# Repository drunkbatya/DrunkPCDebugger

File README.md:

# DrunkPC Debugger
A debugger and flasher for [DrunkPC](https://github.com/drunkbatya/DrunkPC)

<picture>
    
</picture>

## How to use

## How to build firmware

## How to cli tool

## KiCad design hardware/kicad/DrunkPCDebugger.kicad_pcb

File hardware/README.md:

## Errata
### Rev1
`MCU_BUS_DIR` and `BUS_OE\` shared across all 4 transivers, this prevents reading compleately, need to separate

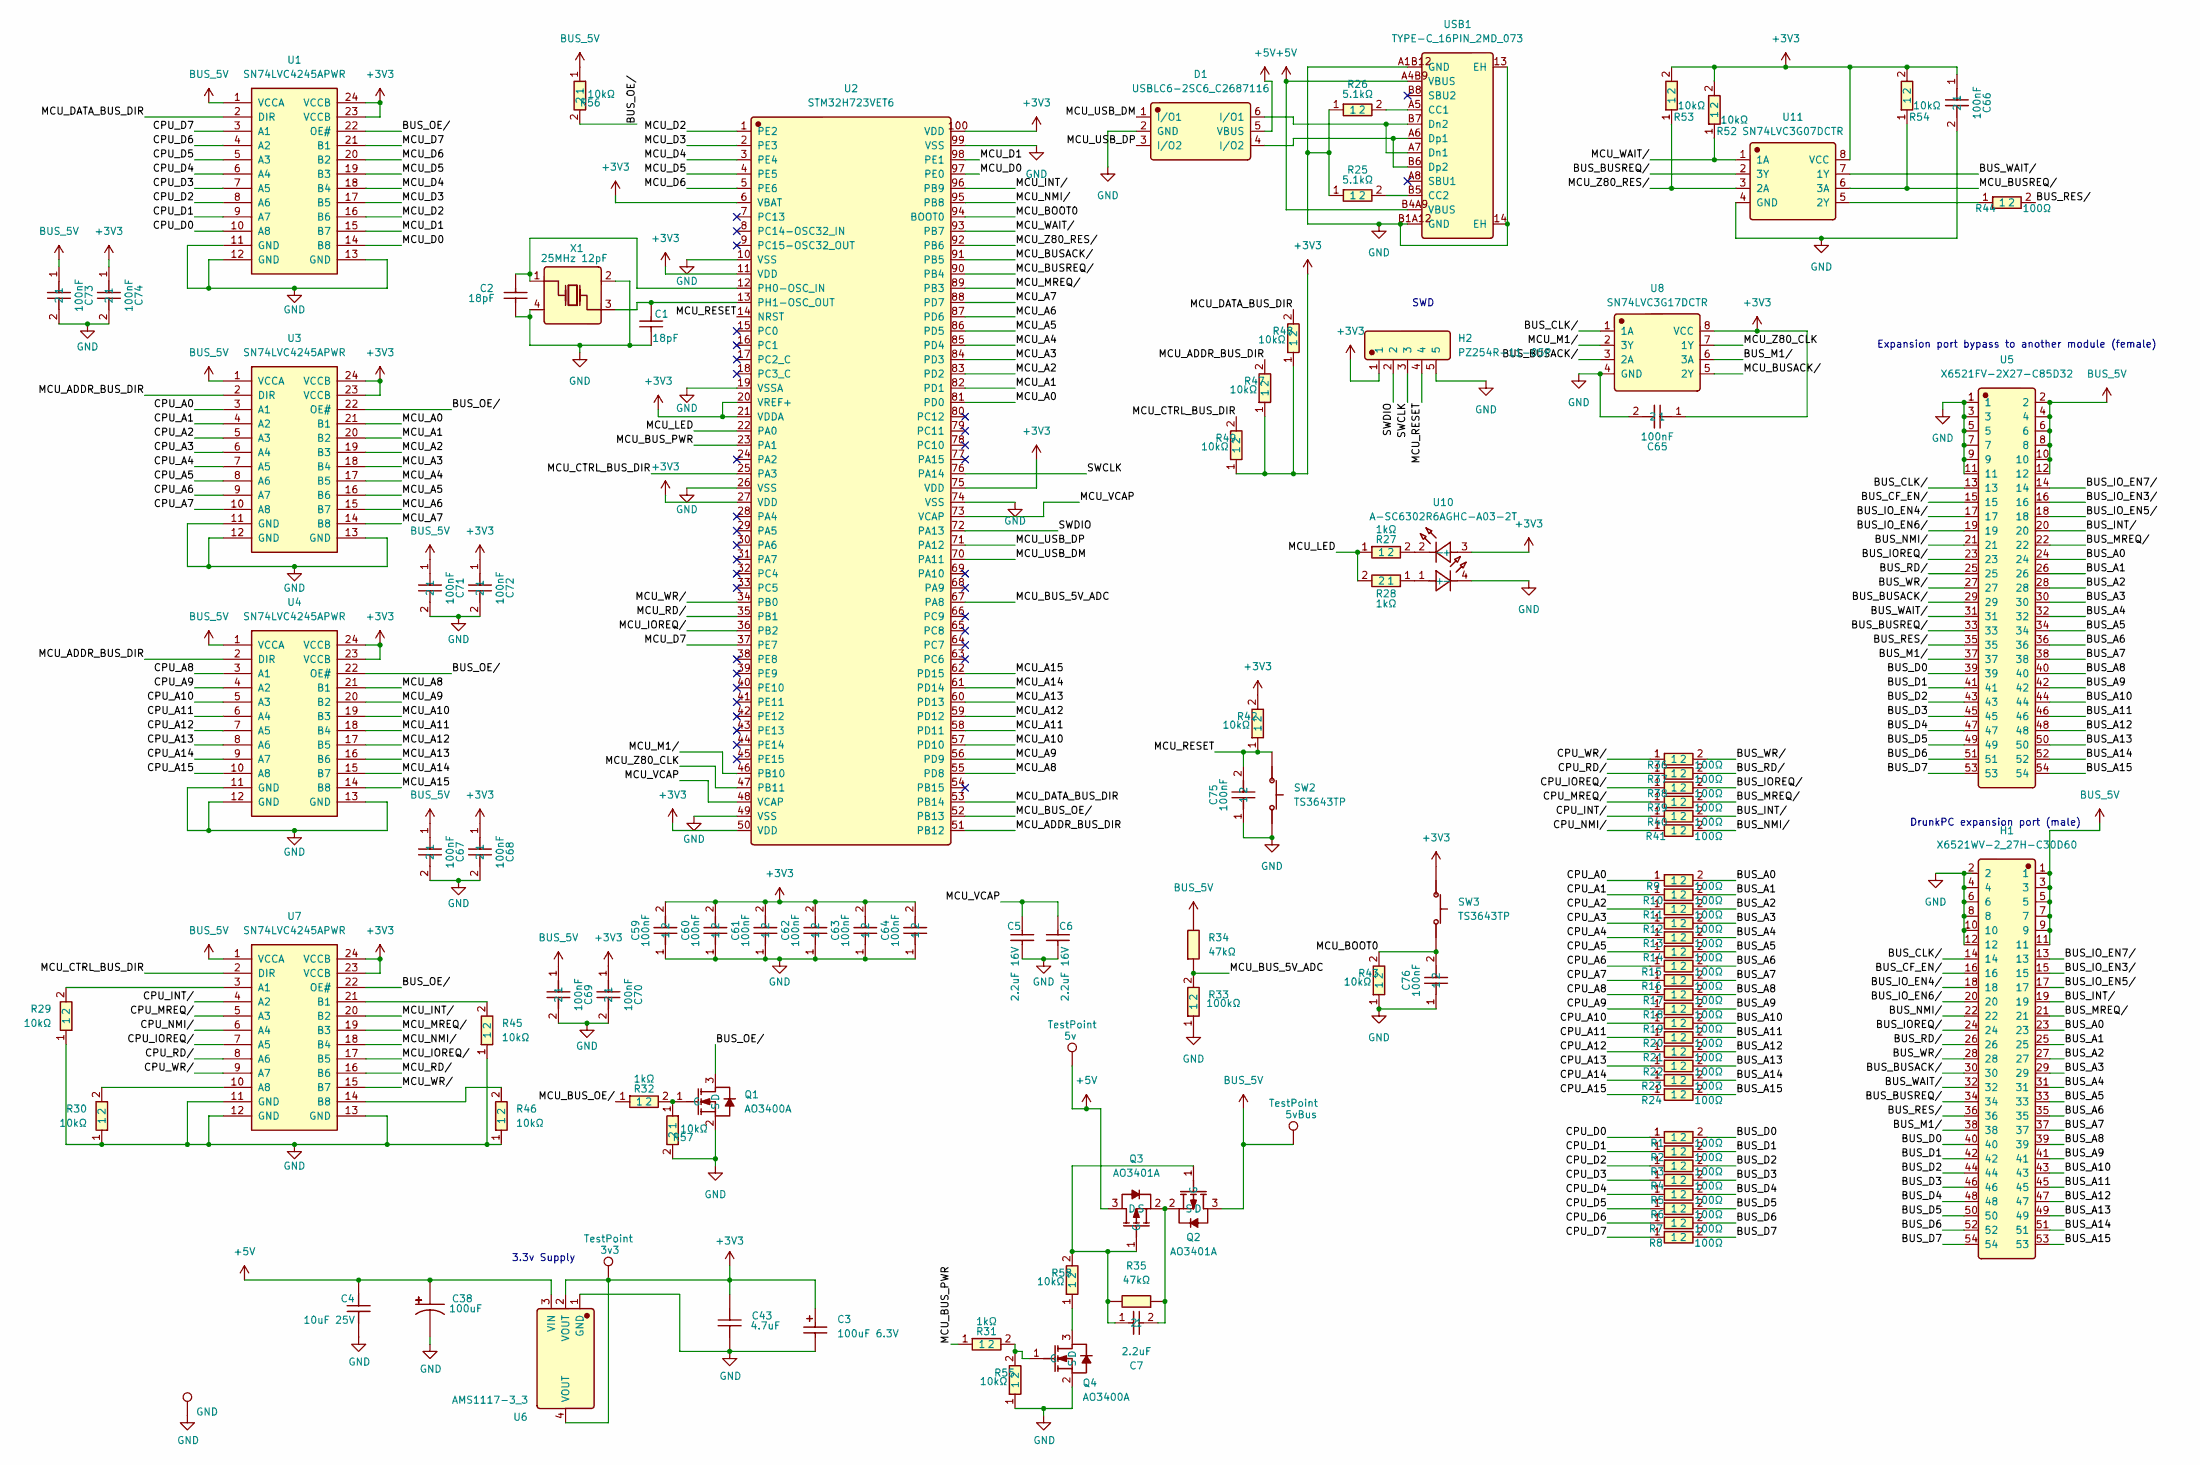
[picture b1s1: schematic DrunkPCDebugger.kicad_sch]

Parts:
3v3_1: 3v3; TestPoint_Pad_D1.5mm
5v_1: 5v; TestPoint_Pad_D1.5mm
5v_bus_1: 5vBus; TestPoint_Pad_D1.5mm
C1, C2: CL10C180JB8NNNC; C_0603_1608Metric; Manufacturer Part CL10C180JB8NNNC; LCSC C1647
C3: 100uF 6.3V; CP_EIA-3528-21_Kemet-B; Manufacturer Part TAJB107K006RNJ; LCSC C16133
C4: 10uF 25V; C_0805_2012Metric; Manufacturer Part CL21A106KAYNNNE; LCSC C15850
C5, C6: 2.2uF 16V; C_0603_1608Metric; Manufacturer Part CL10A225KO8NNNC; LCSC C23630
C7: 2.2uF; C_0603_1608Metric; Manufacturer Part CL10A225KO8NNNC; LCSC C23630
C38: EEFCX0J101R; Manufacturer Part EEFCX0J101R; LCSC C189619
C43: CL10A475KO8NNNC; C_0603_1608Metric; Manufacturer Part CL10A475KO8NNNC; LCSC C19666
C59, C60, C61, C62, C63, C64, C65, C66, C67, C68, C69, C70, C71, C72, C73, C74, C75, C76: CC0603KRX7R9BB104; C_0603_1608Metric; Manufacturer Part CC0603KRX7R9BB104; LCSC C14663
D1: USBLC6-2SC6_C2687116; Manufacturer Part USBLC6-2SC6; LCSC C2687116
GND1: GND; TestPoint_Pad_2.0x2.0mm
H1: X6521WV-2_27H-C30D60; Manufacturer Part X6521WV-2x27H-C60D30; LCSC C725899
H2: PZ254R-11-05P; Manufacturer Part PZ254R-11-05P; LCSC C492413
Q1, Q4: AO3400A; Manufacturer Part AO3400A; LCSC C20917
Q2, Q3: AO3401A; Manufacturer Part AO3401A; LCSC C15127
R1, R2, R3, R4, R5, R6, R7, R8, R9, R10, R11, R12, R13, R14, R15, R16, R17, R18, R19, R20, R21, R22, R23, R24, R36, R37, R38, R39, R40, R41, R44: 0603WAF1000T5E; R_0603_1608Metric; Manufacturer Part 0603WAF1000T5E; LCSC C22775
R25, R26: 0603WAF5101T5E; R_0603_1608Metric; Manufacturer Part 0603WAF5101T5E; LCSC C23186
R27, R28, R31, R32: 0603WAF1001T5E; R_0603_1608Metric; Manufacturer Part 0603WAF1001T5E; LCSC C21190
R29, R30, R45, R46: 10kΩ; R_0603_1608Metric; Manufacturer Part 0603WAF1002T5E; LCSC C25804
R33: 0603WAF1003T5E; R_0603_1608Metric; Manufacturer Part 0603WAF1003T5E; LCSC C25803
R34, R35: 47kΩ; R_0603_1608Metric; Manufacturer Part 0603WAF4702T5E; LCSC C25819
R42, R43, R47, R48, R49, R52, R53, R54, R55, R56, R57, R58: 0603WAF1002T5E; R_0603_1608Metric; Manufacturer Part 0603WAF1002T5E; LCSC C25804
SW2, SW3: TS3643TP; Manufacturer Part TS3643TP; LCSC C398054
U1, U3, U4, U7: SN74LVC4245APWR; Manufacturer Part SN74LVC4245APWR; LCSC C7859
U2: STM32H723VET6; Manufacturer Part STM32H723VET6; LCSC C730141
U5: X6521FV-2X27-C85D32; Manufacturer Part X6521FV-2x27-C85D32; LCSC C2884000
U6: AMS1117-3_3; Manufacturer Part AMS1117-3.3; LCSC C6186
U8: SN74LVC3G17DCTR; Manufacturer Part SN74LVC3G17DCTR; LCSC C18213
U10: A-SC6302R6AGHC-A03-2T; Manufacturer Part A-SC6302R6AGHC-A03-2T; LCSC C5355456
U11: SN74LVC3G07DCTR; Manufacturer Part SN74LVC3G07DCTR; LCSC C131914
USB1: TYPE-C_16PIN_2MD_073; Manufacturer Part TYPE-C 16PIN 2MD(073); LCSC C2765186
X1: X322525MOB4SI; Crystal_SMD_3225-4Pin_3.2x2.5mm; Manufacturer Part X322525MOB4SI; LCSC C9006

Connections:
+3V3: 3v3_1.1 (1_1), C3.1, C43.2, C59.2, C60.2, C61.2, C62.2, C63.2, C64.2, C65.1, C66.1, C68.1, C70.1, C72.1, C74.1, H2.1, R42.2, R47.1, R48.1, R49.1, R52.2, R53.2, R54.2, SW3.1, U1.23 (VCCB), U1.24 (VCCB), U2.6 (VBAT), U2.11 (VDD), U2.20 (VREF+), U2.21 (VDDA), U2.27 (VDD), U2.50 (VDD), U2.75 (VDD), U2.100 (VDD), U3.23 (VCCB), U3.24 (VCCB), U4.23 (VCCB), U4.24 (VCCB), U6.2 (VOUT), U6.4 (VOUT), U7.23 (VCCB), U7.24 (VCCB), U8.8 (VCC), U10.3 (+), U11.8 (VCC)
+5V: 5v_1.1 (1_1), C4.1, C38.1, D1.5 (VBUS), Q3.3 (D), U6.3 (VIN), USB1.A4B9 (VBUS), USB1.B4A9 (VBUS)
/BUS_A0: H1.23, R9.2, U5.24
/BUS_A1: H1.25, R10.2, U5.26
/BUS_A2: H1.27, R11.2, U5.28
/BUS_A3: H1.29, R12.2, U5.30
/BUS_A4: H1.31, R13.2, U5.32
/BUS_A5: H1.33, R14.2, U5.34
/BUS_A6: H1.35, R15.2, U5.36
/BUS_A7: H1.37, R16.2, U5.38
/BUS_A8: H1.39, R17.2, U5.40
/BUS_A9: H1.41, R18.2, U5.42
/BUS_A10: H1.43, R19.2, U5.44
/BUS_A11: H1.45, R20.2, U5.46
/BUS_A12: H1.47, R21.2, U5.48
/BUS_A13: H1.49, R22.2, U5.50
/BUS_A14: H1.51, R23.2, U5.52
/BUS_A15: H1.53, R24.2, U5.54
/BUS_BUSACK/: H1.30, U5.29, U8.3 (2A)
/BUS_BUSREQ/: H1.34, U5.33, U11.2 (3Y)
/BUS_CF_EN/: H1.16, U5.15
/BUS_CLK/: H1.14, U5.13, U8.1 (1A)
/BUS_D0: H1.40, R1.2, U5.39
/BUS_D1: H1.42, R2.2, U5.41
/BUS_D2: H1.44, R3.2, U5.43
/BUS_D3: H1.46, R4.2, U5.45
/BUS_D4: H1.48, R5.2, U5.47
/BUS_D5: H1.50, R6.2, U5.49
/BUS_D6: H1.52, R7.2, U5.51
/BUS_D7: H1.54, R8.2, U5.53
/BUS_INT/: H1.19, R40.2, U5.20
/BUS_IOREQ/: H1.24, R38.2, U5.23
/BUS_IO_EN3/: H1.15, U5.16
/BUS_IO_EN4/: H1.18, U5.17
/BUS_IO_EN5/: H1.17, U5.18
/BUS_IO_EN6/: H1.20, U5.19
/BUS_IO_EN7/: H1.13, U5.14
/BUS_M1/: H1.38, U5.37, U8.6 (3A)
/BUS_MREQ/: H1.21, R39.2, U5.22
/BUS_NMI/: H1.22, R41.2, U5.21
/BUS_OE/: Q1.3 (D), R56.2, U1.22 (OE#), U3.22 (OE#), U4.22 (OE#), U7.22 (OE#)
/BUS_RD/: H1.26, R37.2, U5.25
/BUS_RES/: H1.36, R44.2, U5.35
/BUS_WAIT/: H1.32, U5.31, U11.7 (1Y)
/BUS_WR/: H1.28, R36.2, U5.27
/CPU_A0: R9.1, U3.3 (A1)
/CPU_A1: R10.1, U3.4 (A2)
/CPU_A2: R11.1, U3.5 (A3)
/CPU_A3: R12.1, U3.6 (A4)
/CPU_A4: R13.1, U3.7 (A5)
/CPU_A5: R14.1, U3.8 (A6)
/CPU_A6: R15.1, U3.9 (A7)
/CPU_A7: R16.1, U3.10 (A8)
/CPU_A8: R17.1, U4.3 (A1)
/CPU_A9: R18.1, U4.4 (A2)
/CPU_A10: R19.1, U4.5 (A3)
/CPU_A11: R20.1, U4.6 (A4)
/CPU_A12: R21.1, U4.7 (A5)
/CPU_A13: R22.1, U4.8 (A6)
/CPU_A14: R23.1, U4.9 (A7)
/CPU_A15: R24.1, U4.10 (A8)
/CPU_D0: R1.1, U1.10 (A8)
/CPU_D1: R2.1, U1.9 (A7)
/CPU_D2: R3.1, U1.8 (A6)
/CPU_D3: R4.1, U1.7 (A5)
/CPU_D4: R5.1, U1.6 (A4)
/CPU_D5: R6.1, U1.5 (A3)
/CPU_D6: R7.1, U1.4 (A2)
/CPU_D7: R8.1, U1.3 (A1)
/CPU_INT/: R40.1, U7.4 (A2)
/CPU_IOREQ/: R38.1, U7.7 (A5)
/CPU_MREQ/: R39.1, U7.5 (A3)
/CPU_NMI/: R41.1, U7.6 (A4)
/CPU_RD/: R37.1, U7.8 (A6)
/CPU_WR/: R36.1, U7.9 (A7)
/MCU_A0: U2.81 (PD0), U3.21 (B1)
/MCU_A1: U2.82 (PD1), U3.20 (B2)
/MCU_A2: U2.83 (PD2), U3.19 (B3)
/MCU_A3: U2.84 (PD3), U3.18 (B4)
/MCU_A4: U2.85 (PD4), U3.17 (B5)
/MCU_A5: U2.86 (PD5), U3.16 (B6)
/MCU_A6: U2.87 (PD6), U3.15 (B7)
/MCU_A7: U2.88 (PD7), U3.14 (B8)
/MCU_A8: U2.55 (PD8), U4.21 (B1)
/MCU_A9: U2.56 (PD9), U4.20 (B2)
/MCU_A10: U2.57 (PD10), U4.19 (B3)
/MCU_A11: U2.58 (PD11), U4.18 (B4)
/MCU_A12: U2.59 (PD12), U4.17 (B5)
/MCU_A13: U2.60 (PD13), U4.16 (B6)
/MCU_A14: U2.61 (PD14), U4.15 (B7)
/MCU_A15: U2.62 (PD15), U4.14 (B8)
/MCU_ADDR_BUS_DIR: R47.2, U2.51 (PB12), U3.2 (DIR), U4.2 (DIR)
/MCU_BOOT0: C76.2, R43.2, SW3.2, U2.94 (BOOT0)
/MCU_BUSACK/: U2.91 (PB5), U8.5 (2Y)
/MCU_BUSREQ/: R54.1, U2.90 (PB4), U11.6 (3A)
/MCU_BUS_5V_ADC: R33.2, R34.1, U2.67 (PA8)
/MCU_BUS_OE/: R32.1, U2.52 (PB13)
/MCU_BUS_PWR: R31.1, U2.23 (PA1)
/MCU_CTRL_BUS_DIR: R49.2, U2.25 (PA3), U7.2 (DIR)
/MCU_D0: U1.14 (B8), U2.97 (PE0)
/MCU_D1: U1.15 (B7), U2.98 (PE1)
/MCU_D2: U1.16 (B6), U2.1 (PE2)
/MCU_D3: U1.17 (B5), U2.2 (PE3)
/MCU_D4: U1.18 (B4), U2.3 (PE4)
/MCU_D5: U1.19 (B3), U2.4 (PE5)
/MCU_D6: U1.20 (B2), U2.5 (PE6)
/MCU_D7: U1.21 (B1), U2.37 (PE7)
/MCU_DATA_BUS_DIR: R48.2, U1.2 (DIR), U2.53 (PB14)
/MCU_INT/: U2.96 (PB9), U7.20 (B2)
/MCU_IOREQ/: U2.36 (PB2), U7.17 (B5)
/MCU_LED: R27.1, R28.2, U2.22 (PA0)
/MCU_M1/: U2.46 (PB10), U8.2 (3Y)
/MCU_MREQ/: U2.89 (PB3), U7.19 (B3)
/MCU_NMI/: U2.95 (PB8), U7.18 (B4)
/MCU_RD/: U2.35 (PB1), U7.16 (B6)
/MCU_RESET: C75.2, H2.4, R42.1, SW2.1, U2.14 (NRST)
/MCU_USB_DM: D1.1 (I/O1), U2.70 (PA11)
/MCU_USB_DP: D1.3 (I/O2), U2.71 (PA12)
/MCU_VCAP: C5.1, C6.1, U2.48 (VCAP), U2.73 (VCAP)
/MCU_WAIT/: R52.1, U2.93 (PB7), U11.1 (1A)
/MCU_WR/: U2.34 (PB0), U7.15 (B7)
/MCU_Z80_CLK: U2.47 (PB11), U8.7 (1Y)
/MCU_Z80_RES/: R53.1, U2.92 (PB6), U11.3 (2A)
/SWCLK: H2.3, U2.76 (PA14)
/SWDIO: H2.2, U2.72 (PA13)
BUS_5V: 5v_bus_1.1 (1_1), C67.1, C69.1, C71.1, C73.1, H1.1, H1.3, H1.5, H1.7, H1.9, H1.11, Q2.3 (D), R34.2, R56.1, U1.1 (VCCA), U3.1 (VCCA), U4.1 (VCCA), U5.2, U5.4, U5.6, U5.8, U5.10, U5.12, U7.1 (VCCA)
GND: C1.2, C2.2, C3.2, C4.2, C5.2, C6.2, C38.2, C43.1, C59.1, C60.1, C61.1, C62.1, C63.1, C64.1, C65.2, C66.2, C67.2, C68.2, C69.2, C70.2, C71.2, C72.2, C73.2, C74.2, C75.1, C76.1, D1.2 (GND), GND1.1 (1_1), H1.2, H1.4, H1.6, H1.8, H1.10, H1.12, H2.5, Q1.2 (S), Q4.2 (S), R25.1, R26.1, R29.1, R30.1, R33.1, R43.1, R45.1, R46.1, R55.1, R57.2, SW2.2, U1.11 (GND), U1.12 (GND), U1.13 (GND), U2.10 (VSS), U2.19 (VSSA), U2.26 (VSS), U2.49 (VSS), U2.74 (VSS), U2.99 (VSS), U3.11 (GND), U3.12 (GND), U3.13 (GND), U4.11 (GND), U4.12 (GND), U4.13 (GND), U5.1, U5.3, U5.5, U5.7, U5.9, U5.11, U6.1 (GND), U7.11 (GND), U7.12 (GND), U7.13 (GND), U8.4 (GND), U10.4 (-), U11.4 (GND), USB1.13 (EH), USB1.14 (EH), USB1.A1B12 (GND), USB1.B1A12 (GND), X1.2 (GND), X1.4 (GND)
unnamed: Q1.1 (G), R32.2, R57.1
unnamed: C7.1, Q2.1 (G), Q3.1 (G), R35.2, R58.2
unnamed: C7.2, Q2.2 (S), Q3.2 (S), R35.1
unnamed: Q4.3 (D), R58.1
unnamed: Q4.1 (G), R31.2, R55.2
unnamed: R27.2, U10.2 (-)
unnamed: R28.1, U10.1 (+)
unnamed: C2.1, U2.12 (PH0-OSC_IN), X1.1 (OSC1)
unnamed: C1.1, U2.13 (PH1-OSC_OUT), X1.3 (OSC2)
unnamed: R29.2, U7.3 (A1)
unnamed: R30.2, U7.10 (A8)
unnamed: R45.2, U7.21 (B1)
unnamed: R46.2, U7.14 (B8)
unnamed: R44.1, U11.5 (2Y)
unnamed: R26.2, USB1.A5 (CC1)
unnamed: R25.2, USB1.B5 (CC2)
unnamed: D1.6 (I/O1), USB1.A7 (Dn1), USB1.B7 (Dn2)
unnamed: D1.4 (I/O2), USB1.A6 (Dp1), USB1.B6 (Dp2)

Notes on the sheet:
SWD
DrunkPC expansion port (male)
3.3v Supply
Expansion port bypass to another module (female)

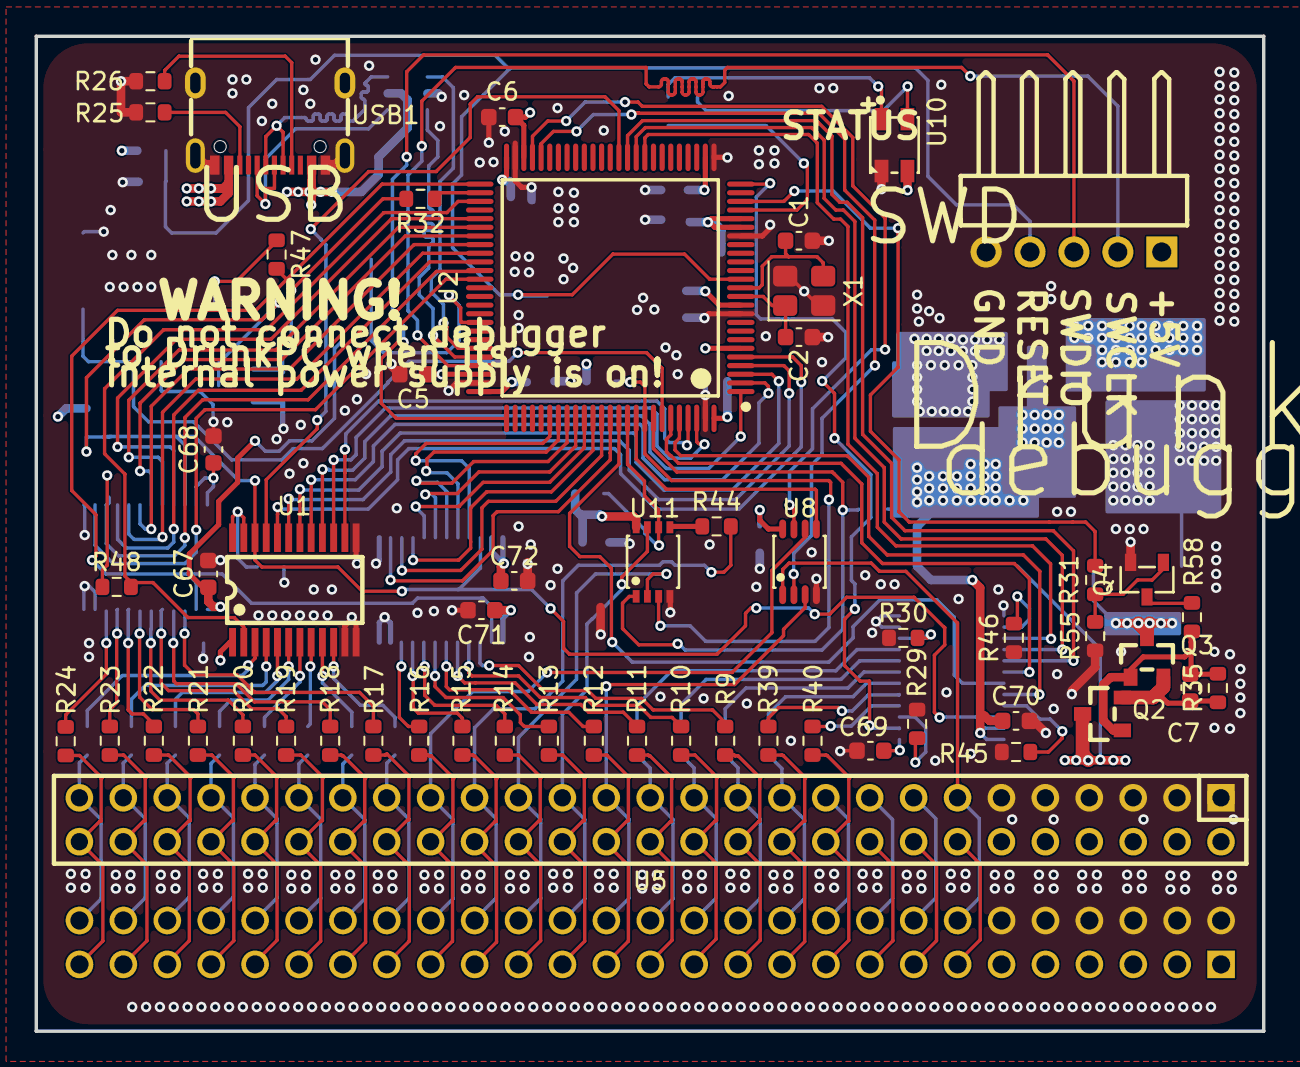
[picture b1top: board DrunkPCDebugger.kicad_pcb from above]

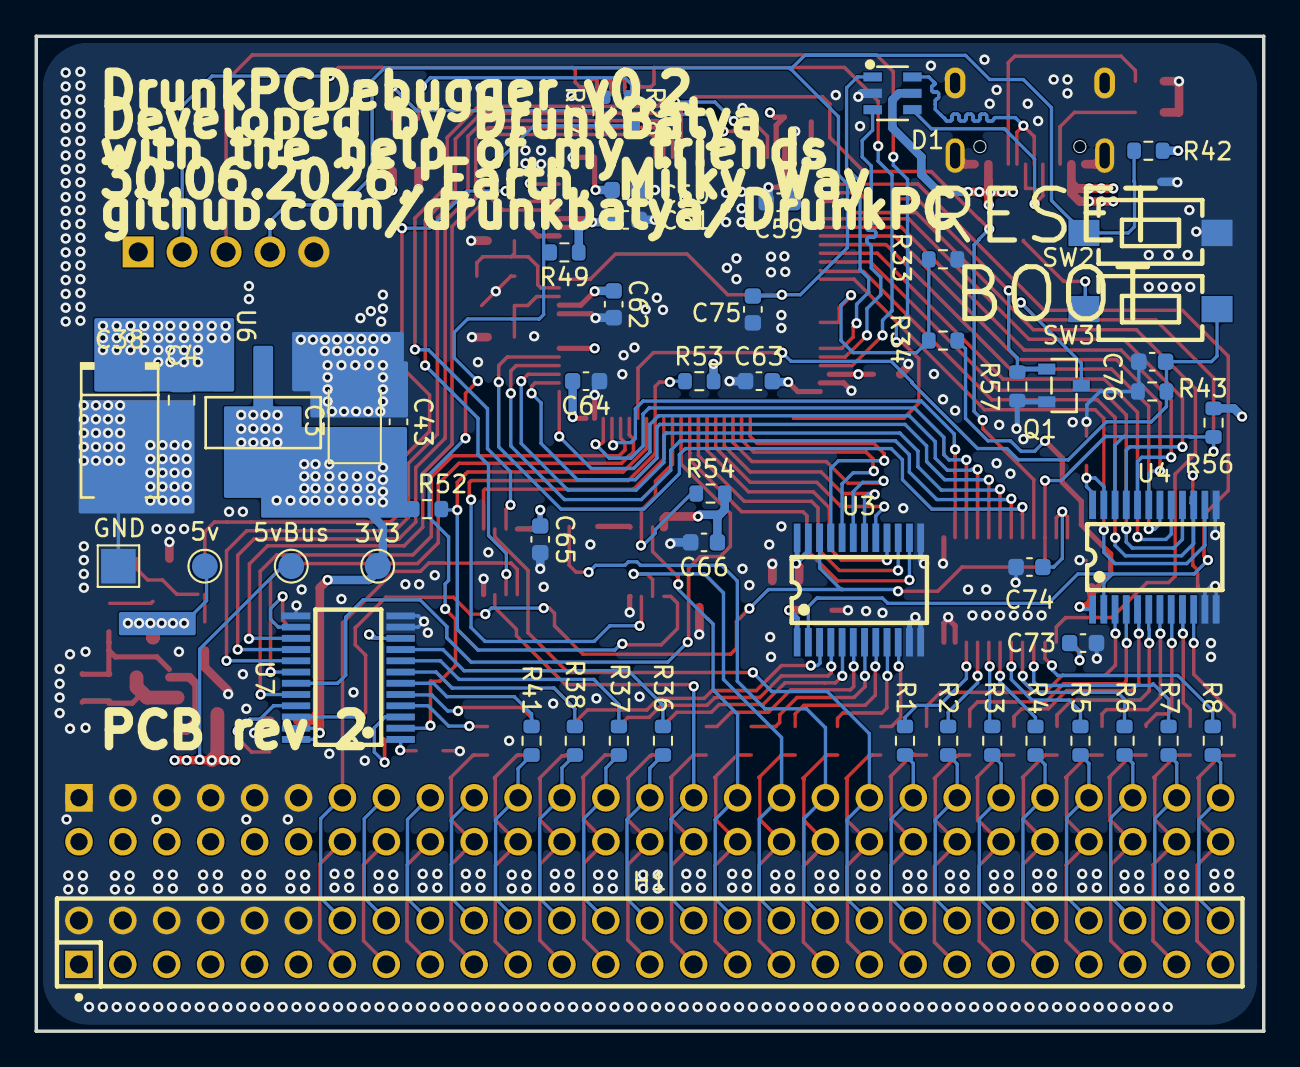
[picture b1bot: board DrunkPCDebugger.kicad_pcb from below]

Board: 4 copper layers, 71.0 x 57.5 mm, 108 parts (53 on the bottom side), 145 nets.

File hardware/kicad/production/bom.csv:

Designator,Footprint,Quantity,Value,LCSC Part #
3V3_1,TestPoint_Pad_D1.5mm,1,3v3,
5V_1,TestPoint_Pad_D1.5mm,1,5v,
5V_BUS_1,TestPoint_Pad_D1.5mm,1,5vBus,
"C1, C2",0603,2,CL10C180JB8NNNC,C1647
"C3, C4",0805,2,GRM21BR71A225KA01L,C117966
C38,EEFCX0J101R,1,EEFCX0J101R,C189619
C39,GCM21BR71A106KE22L,1,GCM21BR71A106KE22L,C126586
C43,0603,1,CL10A475KO8NNNC,C19666
"C5, C6",0603,2,CC0603KRX7R0BB103,C107059
"C59, C60, C61, C62, C63, C64, C65, C66, C67, C68, C69, C70, C71, C72, C73, C74",0603,16,CL10B104KB8NNNC,C1591
C9,25TQC22MYFB,1,25TQC22MYFB,C3018703
GND1,TestPoint_Pad_2.0x2.0mm,1,GND,
H1,X6521WV-2_27H-C30D60,1,X6521WV-2_27H-C30D60,C725899
H2,PZ254R-11-04P,1,PZ254R-11-04P,C492412
Q1,2N7002K-T1-GE3,1,2N7002K-T1-GE3,C81445
"Q2, Q3",AO3401A,2,AO3401A,C15127
"R1, R10, R11, R12, R13, R14, R15, R16, R17, R18, R19, R2, R20, R21, R22, R23, R24, R3, R30, R36, R37, R38, R39, R4, R40, R41, R5, R6, R7, R8, R9",0603,31,RT0603BRD07100RL,C122970
"R25, R26",0603,2,FRC0603F5101TS,C2907044
"R27, R28, R31",0603,3,FRC0603F1001TS,C2907002
R29,0603,1,FRC0603J104_TS,C2907088
"R42, R43, R47, R52, R53, R54, R55, R56",0603,8,RT0603BRD0710KL,C95204
"SW2, SW3",TS3643TP,2,TS3643TP,C398054
"U1, U3, U4, U7",74LVX4245MTCX,4,74LVX4245MTCX,C61186
U10,A-SC6302R6AGHC-A03-2T,1,A-SC6302R6AGHC-A03-2T,C5355456
U2,STM32H723VGT6,1,STM32H723VGT6,C730142
U5,X6521FV-2X27-C85D32,1,X6521FV-2X27-C85D32,C2884000
U6,AMS1117-3_3,1,AMS1117-3_3,C6186
U8,SN74LVC3G17DCTR,1,SN74LVC3G17DCTR,C18213
U9,SN74AHCT125DR,1,SN74AHCT125DR,C155176
USB1,TYPE-C_16PIN_2MD_073,1,TYPE-C_16PIN_2MD_073,C2765186
X1,Crystal_SMD_3225-4Pin_3.2x2.5mm,1,X322525MOB4SI,C9006

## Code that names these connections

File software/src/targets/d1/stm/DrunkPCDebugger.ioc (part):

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Mcu.Name=STM32H723VETx
Mcu.Package=LQFP100
Mcu.UserName=STM32H723VETx
PA0.GPIOParameters=GPIO_PuPd,GPIO_Label
PA0.GPIO_Label=LED
PA0.GPIO_PuPd=GPIO_PULLUP
PA0.Signal=S_TIM5_CH1
PA1.GPIOParameters=GPIO_Label
PA1.GPIO_Label=BUS_PWR
PA1.Signal=GPIO_Output
PA11.Mode=Device_Only_FS
PA11.Signal=USB_OTG_HS_DM
PA12.Mode=Device_Only_FS
PA12.Signal=USB_OTG_HS_DP
PA13(JTMS/SWDIO).Mode=Serial_Wire
PA13(JTMS/SWDIO).Signal=DEBUG_JTMS-SWDIO
PA14(JTCK/SWCLK).Mode=Serial_Wire
PA14(JTCK/SWCLK).Signal=DEBUG_JTCK-SWCLK
PA3.GPIOParameters=GPIO_Label
PA3.GPIO_Label=CTRL_BUS_DIR
PA3.Signal=GPIO_Output
PA8.GPIOParameters=GPIO_Label
PA8.GPIO_Label=BUS_5V_SENSE
PA8.Signal=GPIO_Input
PB0.GPIOParameters=GPIO_Label
PB0.GPIO_Label=_WR
PB0.Signal=GPIO_Input
PB1.GPIOParameters=GPIO_Label
PB1.GPIO_Label=_RD
PB1.Signal=GPIO_Input
PB10.GPIOParameters=GPIO_Label
PB10.GPIO_Label=_M1
PB10.Signal=GPIO_Input
PB11.GPIOParameters=GPIO_Label
PB11.GPIO_Label=_CPU_CLK
PB11.Signal=S_TIM2_CH4
PB12.GPIOParameters=GPIO_Label
PB12.GPIO_Label=ADDR_BUS_DIR
PB12.Signal=GPIO_Output
PB13.GPIOParameters=GPIO_Label
PB13.GPIO_Label=BUS_OE
PB13.Signal=GPIO_Output
PB14.GPIOParameters=GPIO_Label
PB14.GPIO_Label=DATA_BUS_DIR
PB14.Signal=GPIO_Output
PB2.GPIOParameters=GPIO_Label
PB2.GPIO_Label=_IORQ
PB2.Signal=GPIO_Input
PB3(JTDO/TRACESWO).GPIOParameters=GPIO_Label
PB3(JTDO/TRACESWO).GPIO_Label=_MEMRQ
PB3(JTDO/TRACESWO).Signal=GPIO_Input
PB4(NJTRST).GPIOParameters=PinState,GPIO_Label
PB4(NJTRST).GPIO_Label=_BUSREQ
PB4(NJTRST).PinState=GPIO_PIN_SET
PB4(NJTRST).Signal=GPIO_Output
PB5.GPIOParameters=GPIO_Label
PB5.GPIO_Label=_BUSACK
PB5.Signal=GPIO_Input
PB6.GPIOParameters=PinState,GPIO_Label
PB6.GPIO_Label=_CPURST
PB6.PinState=GPIO_PIN_SET
PB6.Signal=GPIO_Output
PB7.GPIOParameters=GPIO_PuPd,GPIO_Label
PB7.GPIO_Label=_WAIT
PB7.GPIO_PuPd=GPIO_PULLUP
PB7.Signal=GPIO_Output
PB8.GPIOParameters=GPIO_PuPd,GPIO_Label
PB8.GPIO_Label=_NMI
PB8.GPIO_PuPd=GPIO_PULLUP
PB8.Signal=S_TIM16_CH1
PB9.GPIOParameters=GPIO_PuPd,GPIO_Label
PB9.GPIO_Label=_INT
PB9.GPIO_PuPd=GPIO_PULLUP
PB9.Signal=S_TIM17_CH1
PD0.GPIOParameters=GPIO_Label
PD0.GPIO_Label=A0
PD0.Signal=GPIO_Input
PD1.GPIOParameters=GPIO_Label
PD1.GPIO_Label=A1
PD1.Signal=GPIO_Input
PD10.GPIOParameters=GPIO_Label
PD10.GPIO_Label=A10
PD10.Signal=GPIO_Input
PD11.GPIOParameters=GPIO_Label
PD11.GPIO_Label=A11
PD11.Signal=GPIO_Input
PD12.GPIOParameters=GPIO_Label
PD12.GPIO_Label=A12
PD12.Signal=GPIO_Input
PD13.GPIOParameters=GPIO_Label
PD13.GPIO_Label=A13
PD13.Signal=GPIO_Input
PD14.GPIOParameters=GPIO_Label
PD14.GPIO_Label=A14
PD14.Signal=GPIO_Input
PD15.GPIOParameters=GPIO_Label
PD15.GPIO_Label=A15
PD15.Signal=GPIO_Input
PD2.GPIOParameters=GPIO_Label
PD2.GPIO_Label=A2
PD2.Signal=GPIO_Input
PD3.GPIOParameters=GPIO_Label
PD3.GPIO_Label=A3
PD3.Signal=GPIO_Input
PD4.GPIOParameters=GPIO_Label
PD4.GPIO_Label=A4
PD4.Signal=GPIO_Input
PD5.GPIOParameters=GPIO_Label
PD5.GPIO_Label=A5
PD5.Signal=GPIO_Input
PD6.GPIOParameters=GPIO_Label
PD6.GPIO_Label=A6
PD6.Signal=GPIO_Input
PD7.GPIOParameters=GPIO_Label
PD7.GPIO_Label=A7
PD7.Signal=GPIO_Input
PD8.GPIOParameters=GPIO_Label
PD8.GPIO_Label=A8
PD8.Signal=GPIO_Input
PD9.GPIOParameters=GPIO_Label
PD9.GPIO_Label=A9
PD9.Signal=GPIO_Input
PE0.GPIOParameters=GPIO_Label
PE0.GPIO_Label=D0
PE0.Signal=GPIO_Input
PE1.GPIOParameters=GPIO_Label
PE1.GPIO_Label=D1
PE1.Signal=GPIO_Input
PE2.GPIOParameters=GPIO_Label
PE2.GPIO_Label=D2
PE2.Signal=GPIO_Input
PE3.GPIOParameters=GPIO_Label
PE3.GPIO_Label=D3
PE3.Signal=GPIO_Input
PE4.GPIOParameters=GPIO_Label
PE4.GPIO_Label=D4
PE4.Signal=GPIO_Input
PE5.GPIOParameters=GPIO_Label
PE5.GPIO_Label=D5
PE5.Signal=GPIO_Input
PE6.GPIOParameters=GPIO_Label
PE6.GPIO_Label=D6
PE6.Signal=GPIO_Input
PE7.GPIOParameters=GPIO_Label
PE7.GPIO_Label=D7
PE7.Signal=GPIO_Input
PH0-OSC_IN.Mode=HSE-External-Oscillator
PH0-OSC_IN.Signal=RCC_OSC_IN
PH1-OSC_OUT.Mode=HSE-External-Oscillator
PH1-OSC_OUT.Signal=RCC_OSC_OUT
RCC.SYSCLKFreq_VALUE=550000000
RCC.SYSCLKSource=RCC_SYSCLKSOURCE_PLLCLK
board=custom

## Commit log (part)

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2026-06-29 Init
2026-06-30 Fix silk
